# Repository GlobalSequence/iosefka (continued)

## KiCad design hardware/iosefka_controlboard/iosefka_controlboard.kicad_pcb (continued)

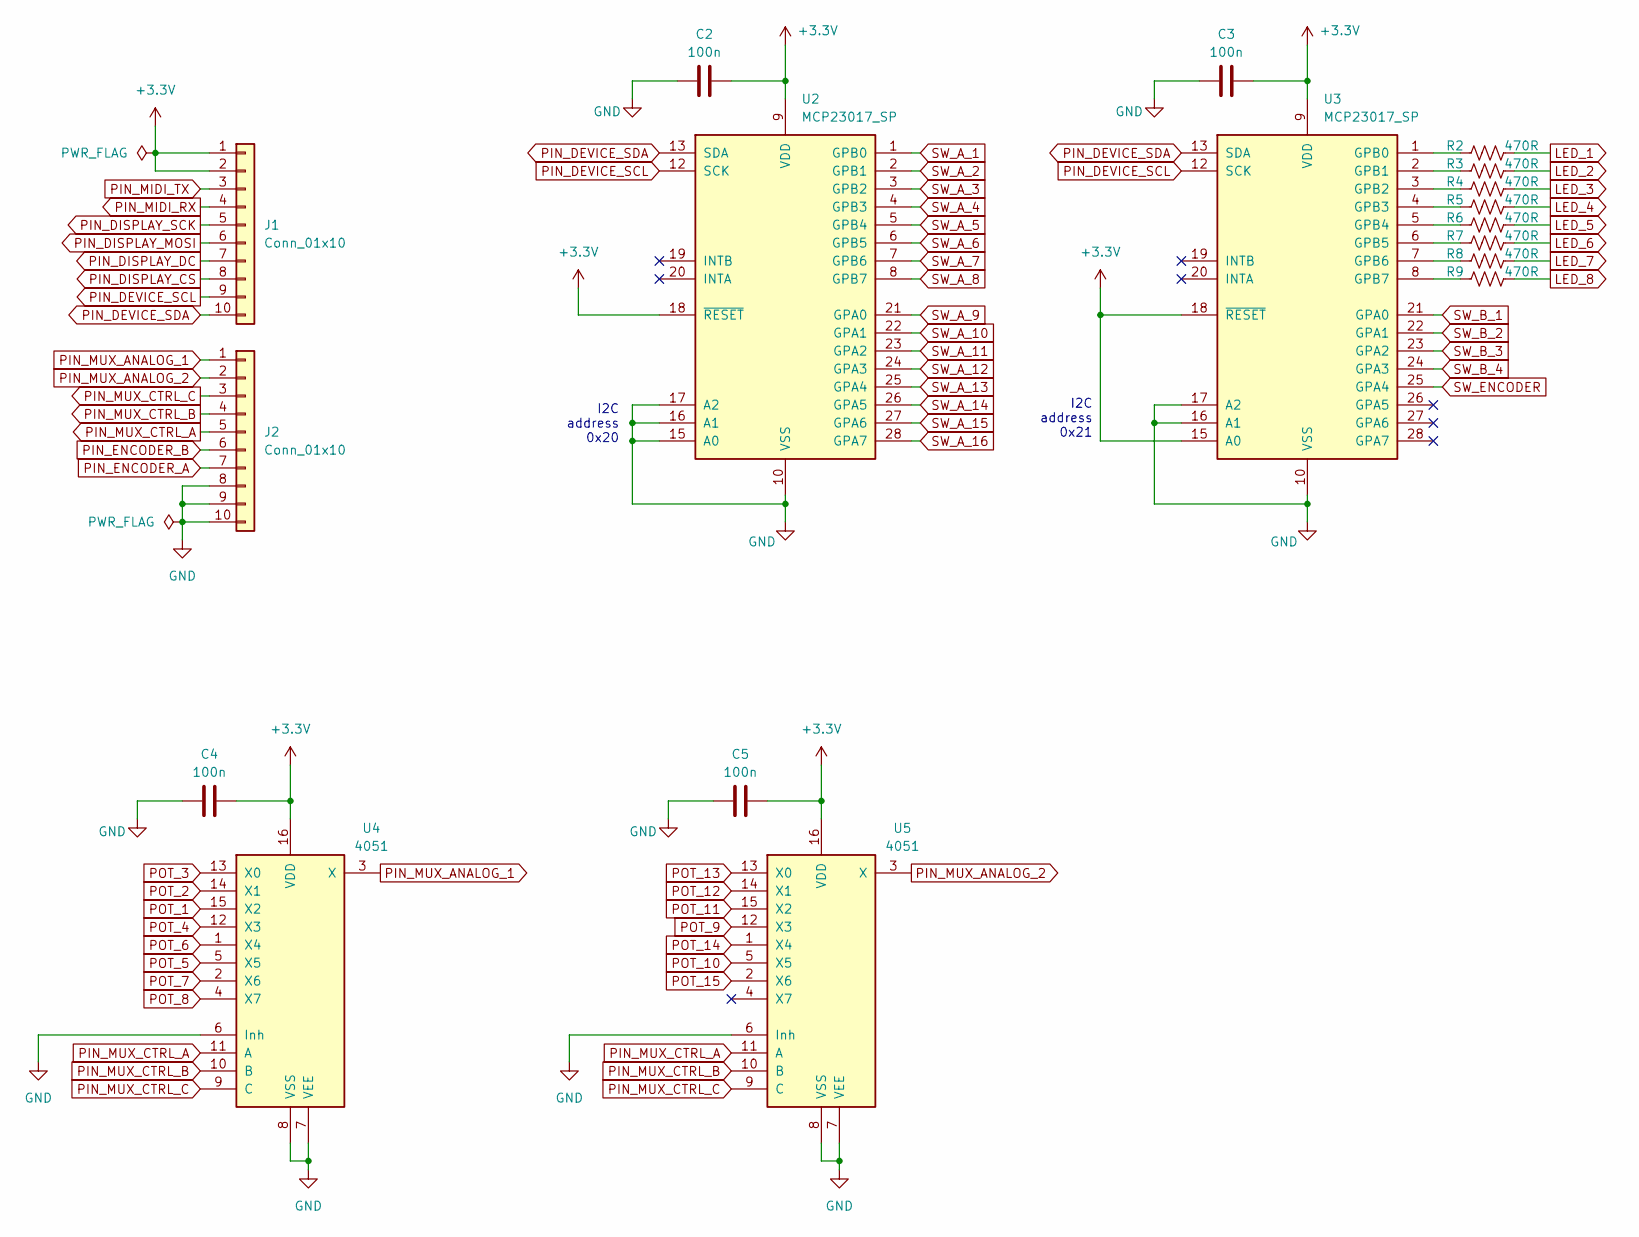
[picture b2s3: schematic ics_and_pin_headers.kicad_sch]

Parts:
C2, C3, C4, C5: 100n; C_Rect_L7.0mm_W2.0mm_P5.00mm
J1, J2: Conn_01x10; PinSocket_1x10_P2.54mm_Vertical
R2, R3, R4, R5, R6, R7, R8, R9: 470R; R_Axial_DIN0207_L6.3mm_D2.5mm_P10.16mm_Horizontal
U2, U3: MCP23017_SP; DIP-28_W7.62mm_Socket
U4, U5: 4051; DIP-16_W7.62mm_Socket

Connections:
+3.3V: C2.2, C3.2, C4.2, C5.2, J1.1, J1.2, U2.9 (VDD), U2.18 (~RESET), U3.9 (VDD), U3.15 (A0), U3.18 (~RESET), U4.16 (VDD), U5.16 (VDD); also elsewhere on the board
GND: C2.1, C3.1, C4.1, C5.1, J2.8, J2.9, J2.10, U2.10 (VSS), U2.15 (A0), U2.16 (A1), U2.17 (A2), U3.10 (VSS), U3.16 (A1), U3.17 (A2), U4.6 (Inh), U4.7 (VEE), U4.8 (VSS), U5.6 (Inh), U5.7 (VEE), U5.8 (VSS); also elsewhere on the board
LED_1: R2.2; also elsewhere on the board
LED_2: R3.2; also elsewhere on the board
LED_3: R4.2; also elsewhere on the board
LED_4: R5.2; also elsewhere on the board
LED_5: R6.2; also elsewhere on the board
LED_6: R7.2; also elsewhere on the board
LED_7: R8.2; also elsewhere on the board
LED_8: R9.2; also elsewhere on the board
unnamed: R2.1, U3.1 (GPB0)
unnamed: R3.1, U3.2 (GPB1)
unnamed: R4.1, U3.3 (GPB2)
unnamed: R5.1, U3.4 (GPB3)
unnamed: R6.1, U3.5 (GPB4)
unnamed: R7.1, U3.6 (GPB5)
unnamed: R8.1, U3.7 (GPB6)
unnamed: R9.1, U3.8 (GPB7)
PIN_DEVICE_SCL: J1.9, U2.12 (SCK), U3.12 (SCK)
PIN_DEVICE_SDA: J1.10, U2.13 (SDA), U3.13 (SDA)
PIN_DISPLAY_CS: J1.8; also elsewhere on the board
PIN_DISPLAY_DC: J1.7; also elsewhere on the board
PIN_DISPLAY_MOSI: J1.6; also elsewhere on the board
PIN_DISPLAY_SCK: J1.5; also elsewhere on the board
PIN_ENCODER_A: J2.7; also elsewhere on the board
PIN_ENCODER_B: J2.6; also elsewhere on the board
PIN_MIDI_RX: J1.4; also elsewhere on the board
PIN_MIDI_TX: J1.3; also elsewhere on the board
PIN_MUX_ANALOG_1: J2.1, U4.3 (X)
PIN_MUX_ANALOG_2: J2.2, U5.3 (X)
PIN_MUX_CTRL_A: J2.5, U4.11 (A), U5.11 (A)
PIN_MUX_CTRL_B: J2.4, U4.10 (B), U5.10 (B)
PIN_MUX_CTRL_C: J2.3, U4.9 (C), U5.9 (C)
POT_1: U4.15 (X2); also elsewhere on the board
POT_2: U4.14 (X1); also elsewhere on the board
POT_3: U4.13 (X0); also elsewhere on the board
POT_4: U4.12 (X3); also elsewhere on the board
POT_5: U4.5 (X5); also elsewhere on the board
POT_6: U4.1 (X4); also elsewhere on the board
POT_7: U4.2 (X6); also elsewhere on the board
POT_8: U4.4 (X7); also elsewhere on the board
POT_9: U5.12 (X3); also elsewhere on the board
POT_10: U5.5 (X5); also elsewhere on the board
POT_11: U5.15 (X2); also elsewhere on the board
POT_12: U5.14 (X1); also elsewhere on the board
POT_13: U5.13 (X0); also elsewhere on the board
POT_14: U5.1 (X4); also elsewhere on the board
POT_15: U5.2 (X6); also elsewhere on the board
SW_A_1: U2.1 (GPB0); also elsewhere on the board
SW_A_2: U2.2 (GPB1); also elsewhere on the board
SW_A_3: U2.3 (GPB2); also elsewhere on the board
SW_A_4: U2.4 (GPB3); also elsewhere on the board
SW_A_5: U2.5 (GPB4); also elsewhere on the board
SW_A_6: U2.6 (GPB5); also elsewhere on the board
SW_A_7: U2.7 (GPB6); also elsewhere on the board
SW_A_8: U2.8 (GPB7); also elsewhere on the board
SW_A_9: U2.21 (GPA0); also elsewhere on the board
SW_A_10: U2.22 (GPA1); also elsewhere on the board
SW_A_11: U2.23 (GPA2); also elsewhere on the board
SW_A_12: U2.24 (GPA3); also elsewhere on the board
SW_A_13: U2.25 (GPA4); also elsewhere on the board
SW_A_14: U2.26 (GPA5); also elsewhere on the board
SW_A_15: U2.27 (GPA6); also elsewhere on the board
SW_A_16: U2.28 (GPA7); also elsewhere on the board
SW_B_1: U3.21 (GPA0); also elsewhere on the board
SW_B_2: U3.22 (GPA1); also elsewhere on the board
SW_B_3: U3.23 (GPA2); also elsewhere on the board
SW_B_4: U3.24 (GPA3); also elsewhere on the board
SW_ENCODER: U3.25 (GPA4); also elsewhere on the board

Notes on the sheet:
I2C address 0x21
I2C address 0x20

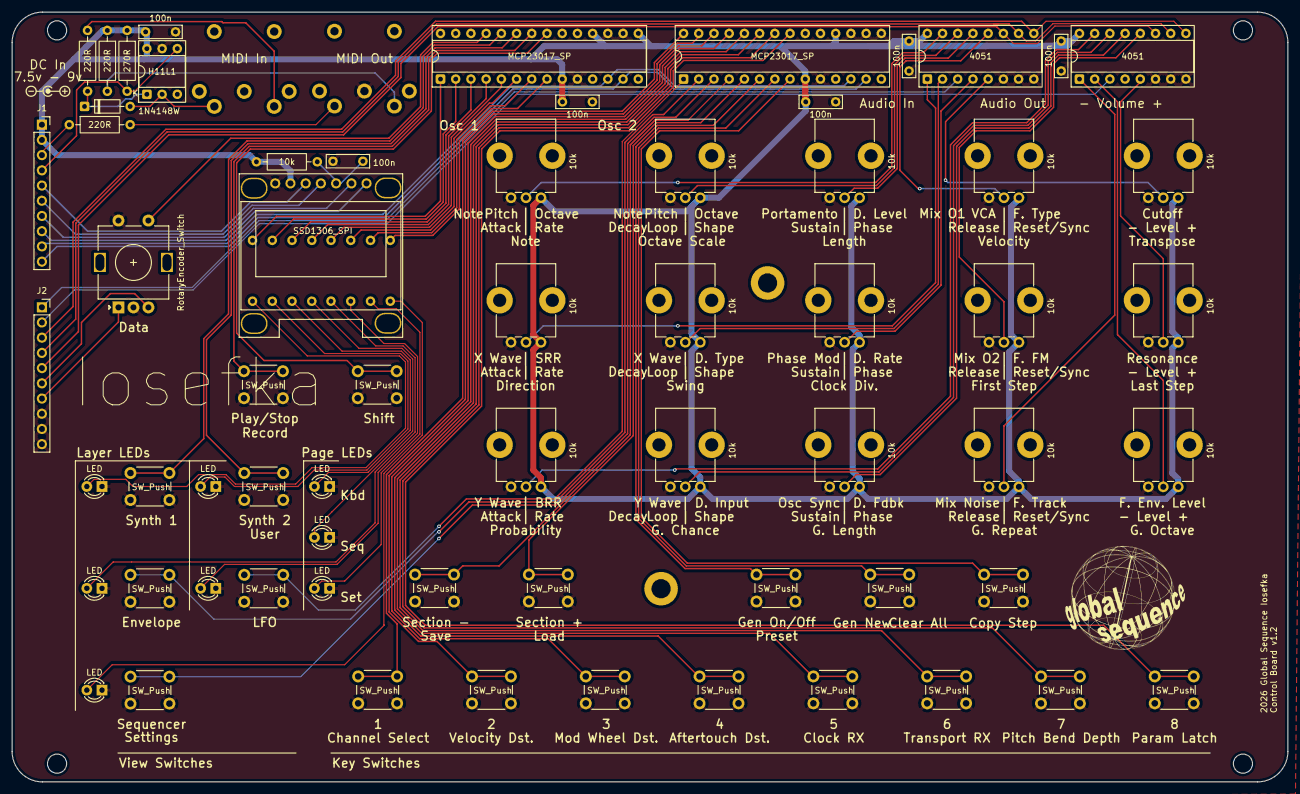
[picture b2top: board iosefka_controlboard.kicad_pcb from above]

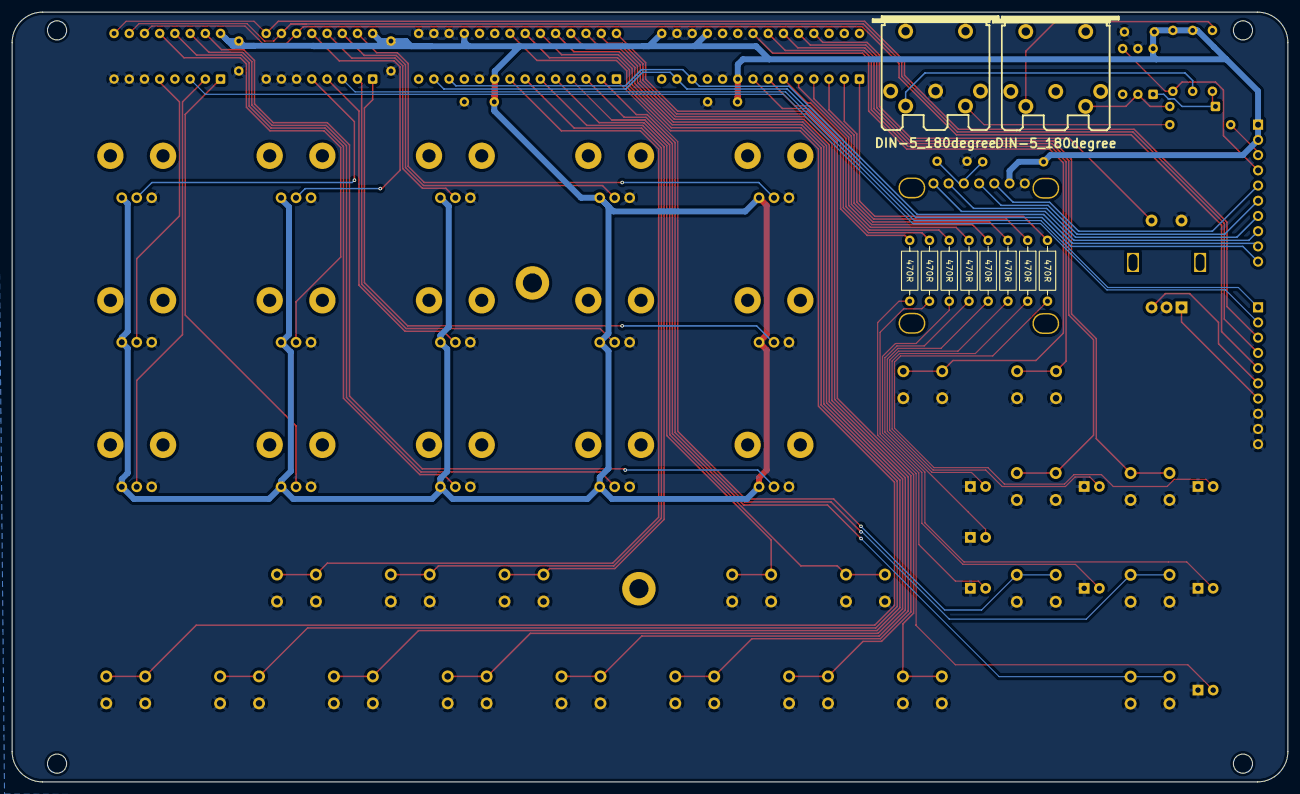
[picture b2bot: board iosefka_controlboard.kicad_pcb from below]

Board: 2 copper layers, 213.0 x 128.5 mm, 74 parts (10 on the bottom side), 75 nets.

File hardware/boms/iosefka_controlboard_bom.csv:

Reference,Value,Datasheet,Footprint,Qty,Comments
"C1,C2,C3,C4,C5,C6",100n,,Capacitor_THT:C_Rect_L7.0mm_W2.0mm_P5.00mm,6,Box capacitors recommended for aesthetic purposes.
"D1,D2,D3,D4,D5,D6,D7,D8","LED, Red",,LED_THT:LED_D3.0mm,8,
D9,1N4148W,https://www.vishay.com/docs/85748/1n4148w.pdf,Diode_THT:D_DO-35_SOD27_P7.62mm_Horizontal,1,
"J1,J2",Conn_01x10,,Connector_PinSocket_2.54mm:PinSocket_1x10_P2.54mm_Vertical,2,"These are 10 pin male headers, not female pin sockets. "
"J3,J6",DIN-5_180degree,http://www.mouser.com/ds/2/18/40_c091_abd_e-75918.pdf,Eurocad:MIDI_DIN5,2,
"R1,RV1,RV2,RV3,RV4,RV5,RV6,RV7,RV8,RV9,RV10,RV11,RV12,RV13,RV14,RV15",10k,,"Potentiometer_THT:Potentiometer_Bourns_PTV09A-1_Single_Vertical,Resistor_THT:R_Axial_DIN0207_L6.3mm_D2.5mm_P10.16mm_Horizontal",15,10k linear potentiometers
"R2,R3,R4,R5,R6,R7,R8,R9",470R,,Resistor_THT:R_Axial_DIN0207_L6.3mm_D2.5mm_P10.16mm_Horizontal,8,"All resistors ¼W, 1% metal film recommended"
"R10,R53,R54",220R,,Resistor_THT:R_Axial_DIN0207_L6.3mm_D2.5mm_P10.16mm_Horizontal,3,
R52,270R,,Resistor_THT:R_Axial_DIN0207_L6.3mm_D2.5mm_P10.16mm_Horizontal,1,
SW1,RotaryEncoder_Switch,,Rotary_Encoder:RotaryEncoder_Alps_EC11E-Switch_Vertical_H20mm,1,"Recommended model: Bourns PEC12R-4225F-S0024. Many encoder models fit this footprint, but note: A lot of encoders I've used had the A and B pins reversed, and turned backwards as a result. "
"SW2,SW3,SW4,SW5,SW6,SW7,SW8,SW9,SW10,SW11,SW12,SW13,SW14,SW15,SW16,SW17,SW18,SW19,SW20,SW21",SW_Push,,Button_Switch_THT:SW_PUSH_6mm,20,Recommended model: E-Switch TL1105BF250Q. These are the red ones.
U1,SSD1306_SPI,,SSD1306:128x64_0.96_Disp_Module,1,"Use a 128x64 SPI display, NOT an I2C. You can tell it's SPI if it has 7 pins. If it has 4 pins, it's an I2C model."
"U2,U3",MCP23017_SP,http://ww1.microchip.com/downloads/en/DeviceDoc/20001952C.pdf,Package_DIP:DIP-28_W7.62mm_Socket,2,
"U4,U5",4051,http://www.intersil.com/content/dam/Intersil/documents/cd40/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,Package_DIP:DIP-16_W7.62mm_Socket,2,
U14,H11L1,https://www.onsemi.com/pub/Collateral/H11L3M-D.PDF,Package_DIP:DIP-6_W7.62mm_Socket,1,
,"28 pin dip socket, 7.26mm row pitch",,,2,
,"16 pin dip socket, 7.26mm row pitch",,,2,
,"6 pin dip socket, 7.26mm row pitch",,,1,

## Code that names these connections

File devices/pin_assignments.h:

// Copyright (C) 2026 Cory Oleson <globeseq@gmail.com>
//
// This program is free software: you can redistribute it and/or modify
// it under the terms of the GNU General Public License as published by
// the Free Software Foundation, either version 3 of the License, or
// (at your option) any later version.
//
// This program is distributed in the hope that it will be useful,
// but WITHOUT ANY WARRANTY; without even the implied warranty of
// MERCHANTABILITY or FITNESS FOR A PARTICULAR PURPOSE.  See the
// GNU General Public License for more details.
//
// You should have received a copy of the GNU General Public License
// along with this program.  If not, see <https://www.gnu.org/licenses/>.

#ifndef PIN_ASSIGNMENTS_H
#define PIN_ASSIGNMENTS_H

// MIDI PINS
#define PIN_MIDI_TX         0
#define PIN_MIDI_RX         1

// GPIO PINS
#define PIN_FIL_SEL_1       2
#define PIN_FIL_SEL_2       3

// I2C DEVICE PINS
#define PIN_DEVICE_SDA      4
#define PIN_DEVICE_SCL      5

// PWM CV PINS
#define PIN_PWM_CUTOFF      6
#define PIN_PWM_RESONANCE   7
#define PIN_PWM_VCA_1       8
#define PIN_PWM_VCA_2       9

// DISPLAY PINS
#define PIN_DISPLAY_SCK     10
#define PIN_DISPLAY_MOSI    11
#define PIN_DISPLAY_DC      12
#define PIN_DISPLAY_CS      13

// ENCODER PINS
#define PIN_ENCODER_A       14
#define PIN_ENCODER_B       15

// AUDIO SPI PINS
#define PIN_AUDIO_MOSI      16
#define PIN_AUDIO_MISO      17
#define PIN_AUDIO_SCK       18
#define PIN_AUDIO_CS        19

// MUX CTRL PINS
#define PIN_MUX_CTRL_A      20
#define PIN_MUX_CTRL_B      21
#define PIN_MUX_CTRL_C      22

// MUX ANALOG PINS
#define PIN_MUX_ANALOG_1    26
#define PIN_MUX_ANALOG_2    27

#endif

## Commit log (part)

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2025-11-30 updated settings
2025-12-10 added user params, srr and brr
2025-12-18 added oscilloscope
2025-12-25 cleanup of some commented sections
2026-02-14 preparing code cleanup
2026-03-20 archiving deprecated oscillator code
2026-03-29 deleted and manually restored folder from zip
2026-04-26 Delay, mod destionation, sequencer features added
2026-04-29 parameter adjustments
2026-04-29 rearranged sequencer parameters
2026-04-30 fixed paraphony and oscillator pitch change issues
2026-05-10 added docs
2026-05-10 removed unwanted submodules
2026-05-10 moved docs to _documentation folder
2026-05-10 Deployed 39b716f with MkDocs version: 1.6.1
2026-05-23 sanity push
2026-05-24 fixed encoder driver
2026-05-31 Deployed 9c9a216 with MkDocs version: 1.6.1
2026-06-02 added MIDI CCs
2026-06-04 Deployed 787f2d4 with MkDocs version: 1.6.1
2026-06-04 fixed modulation errors
2026-06-14 added licenses and readme
2026-06-14 fixed readme typo
2026-06-18 added click on/off setting'
2026-06-18 added to readme and build guide
2026-06-18 Deployed d3444e6 with MkDocs version: 1.6.1
2026-06-19 Deployed 9084158 with MkDocs version: 1.6.1
